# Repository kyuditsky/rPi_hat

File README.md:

9-70VDCin:: 5V 3A Vout buck converter

see buildnotes_rpi_hat.txt for up to date notes/info

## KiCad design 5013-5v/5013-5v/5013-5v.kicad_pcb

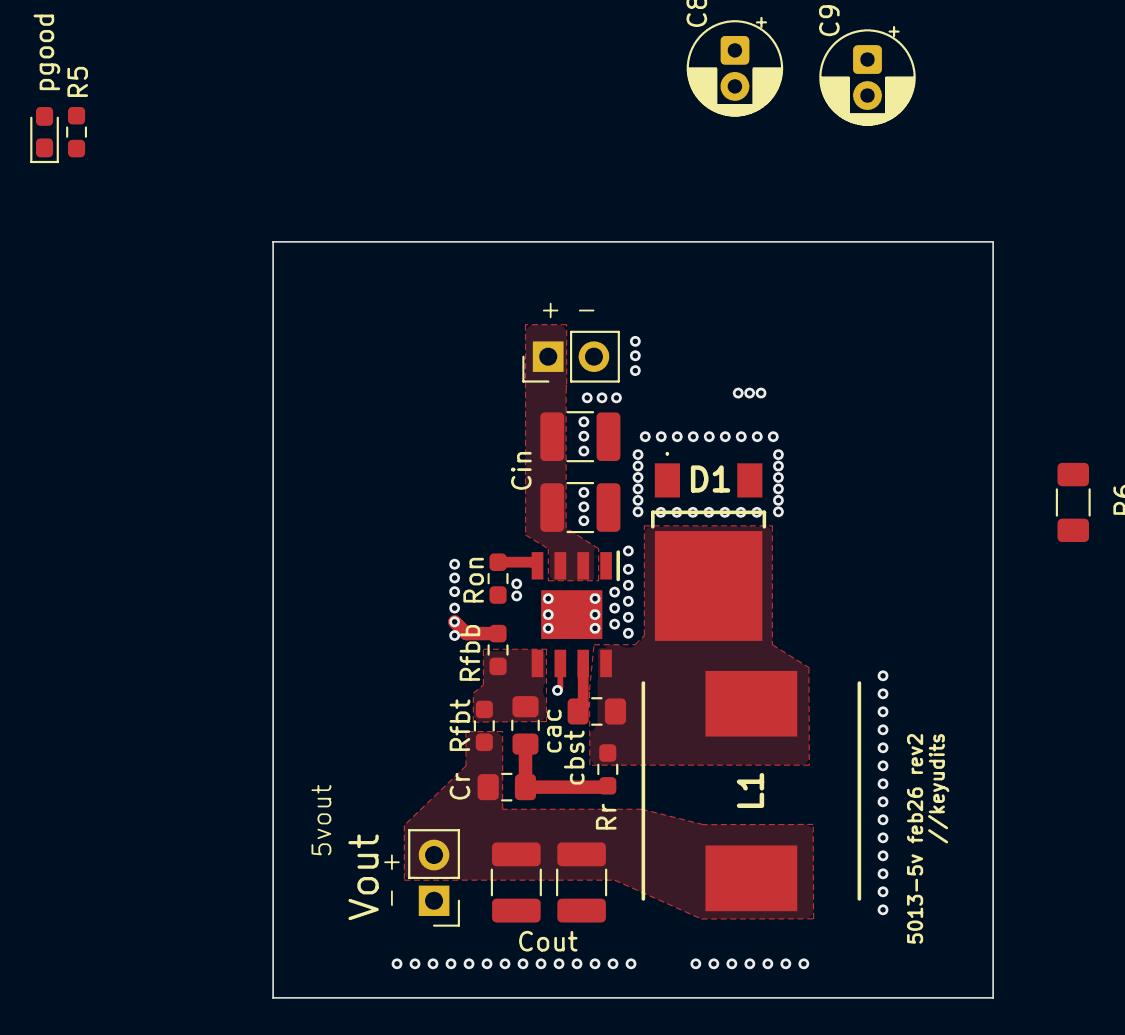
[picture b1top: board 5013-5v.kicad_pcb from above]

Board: 2 copper layers, 40.0 x 42.0 mm, 21 parts (0 on the bottom side), 11 nets.

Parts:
C8, C9: C_Polarized; CP_Radial_D5.0mm_P2.00mm
Cin: 2.2u; C_1210_3225Metric_Pad1.33x2.70mm_HandSolder
Cin#2: 2.2uF; C_1210_3225Metric_Pad1.33x2.70mm_HandSolder
Cout: 22uF; C_1210_3225Metric_Pad1.33x2.70mm_HandSolder
Cout#2: 22uF; C_1210_3225Metric_Pad1.33x2.70mm_HandSolder
Cr: 3.3nF; C_0805_2012Metric_Pad1.18x1.45mm_HandSolder
D1: D_Schottky; TO-252-Ae-3
IC1: LM5013DDAR; SOIC127P600X170-9N
L1: 22uH; INDPM120120X1020N
R5: 2.2k; R_0603_1608Metric_Pad0.98x0.95mm_HandSolder
R6: 0; R_1206_3216Metric_Pad1.30x1.75mm_HandSolder
Rfbb: 49.9kOhm; R_0603_1608Metric_Pad0.98x0.95mm_HandSolder
Rfbt: 158kOhm; R_0603_1608Metric_Pad0.98x0.95mm_HandSolder
Ron: 41.2kOhm; R_0603_1608Metric_Pad0.98x0.95mm_HandSolder
Rr: 154kOhm; R_0603_1608Metric_Pad0.98x0.95mm_HandSolder
Vin: Conn_01x02_Pin; PinHeader_1x02_P2.54mm_Vertical
Vout: Conn_01x02_Pin; PinHeader_1x02_P2.54mm_Vertical
cac: 100pF; C_0805_2012Metric_Pad1.18x1.45mm_HandSolder
cbst: 2.2nF 50v X7R; C_0805_2012Metric_Pad1.18x1.45mm_HandSolder
pgood: LED; LED_0603_1608Metric_Pad1.05x0.95mm_HandSolder

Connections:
/Vin: C8.1, C9.1, Cin.1, Cin#2.1, IC1.2 (VIN), IC1.3 (EN/UVLO), Vin.1
/Vout: Cout.1, Cout#2.1, Cr.2, L1.2, Rfbt.1, Vout.2
/fb: IC1.5 (FB), Rfbb.1, Rfbt.2, cac.2
/sw: D1.1 (K), IC1.8 (SW), L1.1, Rr.1, cbst.1
GND: Cout.2, Cout#2.2, R6.1, Rfbb.2, Vout.1, pgood.1 (K)
GND1: C8.2, C9.2, Cin.2, Cin#2.2, D1.2 (A), IC1.1 (GND), IC1.9 (EP), R6.2, Ron.2, Vin.2
unnamed: Cr.1, Rr.2, cac.1
unnamed: IC1.7 (BST), cbst.2
unnamed: IC1.6 (PGOOD), R5.2
unnamed: IC1.4 (RON), Ron.1
unnamed: R5.1, pgood.2 (A)

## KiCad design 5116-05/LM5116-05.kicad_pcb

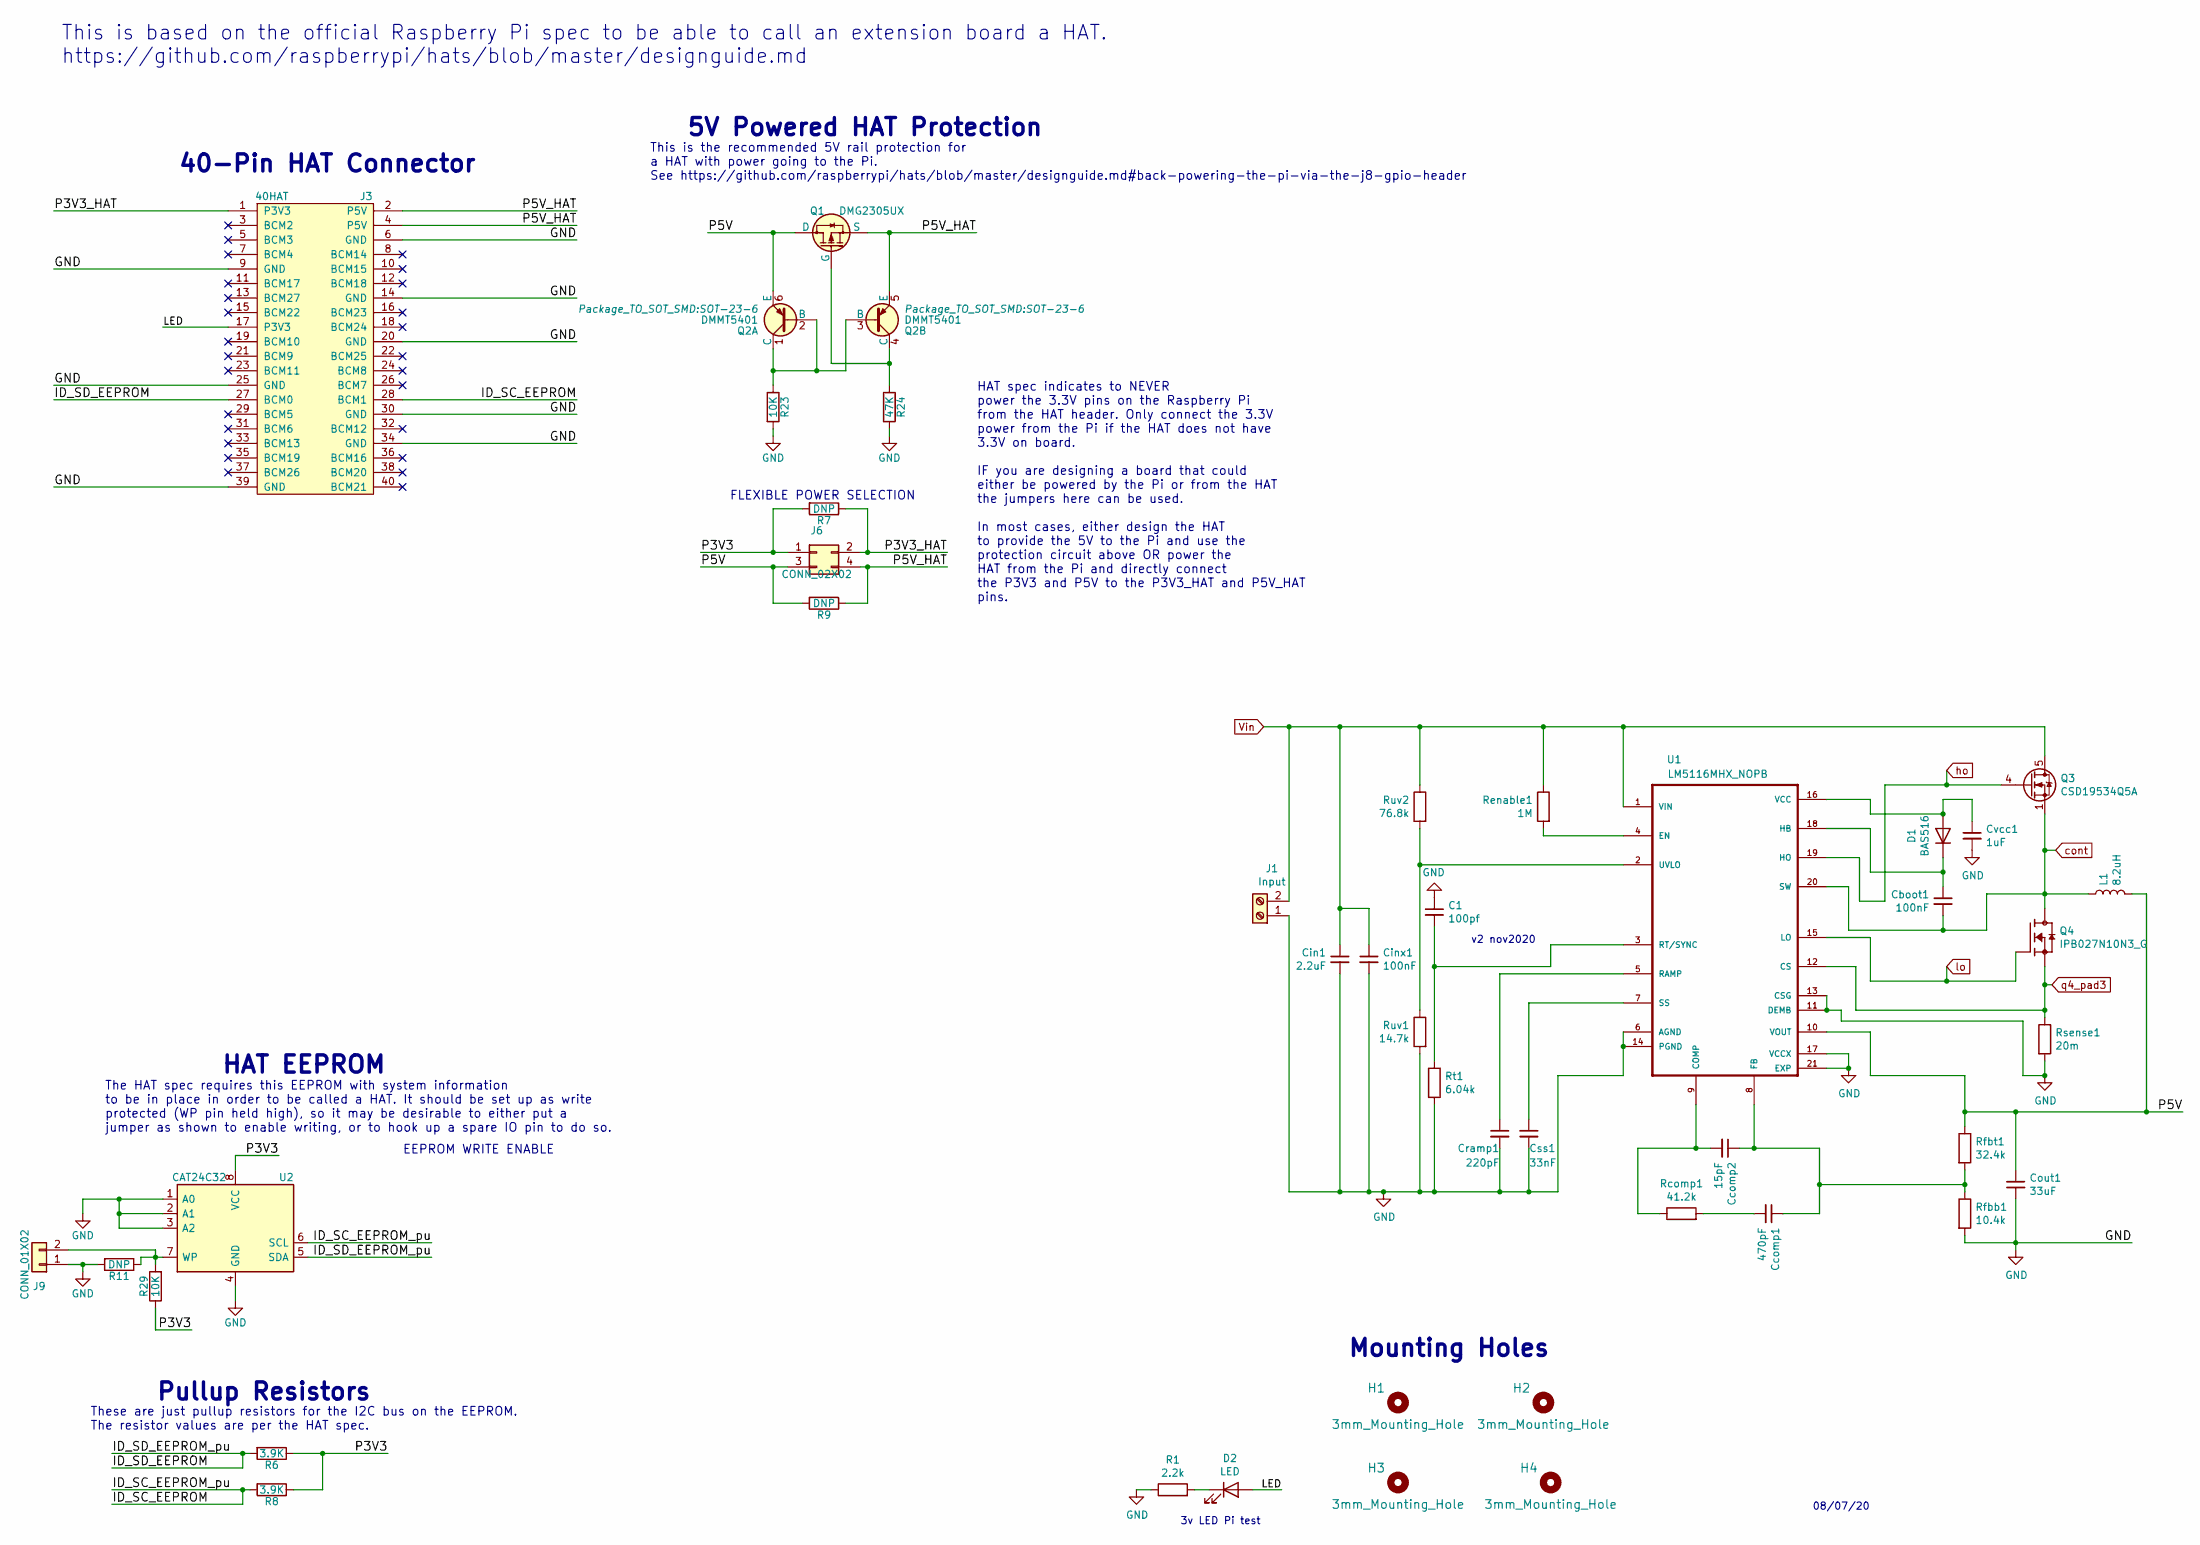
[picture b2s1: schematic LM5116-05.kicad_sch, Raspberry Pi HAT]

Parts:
C1: 100pf; C_Disc_D3.0mm_W2.0mm_P2.50mm
Cboot1: 100nF; C_0402_1005Metric
Ccomp1: 470pF; C_0402_1005Metric
Ccomp2: 15pF; C_0402_1005Metric
Cin1: 2.2uF; C_1210_3225Metric
Cinx1: 100nF; C_0805_2012Metric
Cout1: 33uF; C_1206_3216Metric
Cramp1: 220pF; C_0402_1005Metric
Css1: 33nF; C_0805_2012Metric
Cvcc1: 1uF; C_0805_2012Metric
D1: BAS516; D_SOD-523
D2: LED; LED_0805_2012Metric
H1, H2, H3, H4: 3mm_Mounting_Hole; NPTH_3mm_ID
J1: Input; TerminalBlock_bornier-2_P5.08mm
J3: 40HAT; PinSocket_2x20_P2.54mm_Vertical
J6: CONN_02X02; PinHeader_2x02_P2.54mm_Vertical
J9: CONN_01X02; PinHeader_1x02_P2.54mm_Vertical
L1: 8.2uH; L_Bourns_SRP6540
Q1: DMG2305UX; SOT-23
Q2: DMMT5401; SOT-23-6
Q3: CSD19534Q5A; TDSON-8-1
Q4: IPB027N10N3_G; TO254P1524X457-4N
R1: 2.2k; R_0805_2012Metric
R6, R8: 3.9K; R_0603_1608Metric_Pad0.84x1.00mm_HandSolder
R7, R9, R11: DNP; R_0603_1608Metric_Pad0.84x1.00mm_HandSolder
R23, R29: 10K; R_0603_1608Metric_Pad0.84x1.00mm_HandSolder
R24: 47K; R_0603_1608Metric_Pad0.84x1.00mm_HandSolder
Rcomp1: 41.2k; R_0402_1005Metric
Renable1: 1M; R_0402_1005Metric
Rfbb1: 10.4k; R_0805_2012Metric
Rfbt1: 32.4k; R_0402_1005Metric
Rsense1: 20m; R_1206_3216Metric
Rt1: 6.04k; R_0402_1005Metric
Ruv1: 14.7k; R_0805_2012Metric
Ruv2: 76.8k; R_0805_2012Metric
U1: LM5116MHX_NOPB; SOP65P640X120-21N; Manufacturer_Part_Number LM5116MH/NOPB; Mouser Part Number 926-LM5116MH/NOPB
U2: CAT24C32; SOIC-8_3.9x4.9mm_P1.27mm

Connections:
/ID_SC_EEPROM: J3.28 (BCM1), R8.2, U2.6 (SCL)
/ID_SD_EEPROM: J3.27 (BCM0), R6.2, U2.5 (SDA)
/LED: D2.2 (A), J3.17 (P3V3)
/P3V3: J6.1, R6.1, R7.2, R8.1, R29.1, U2.8 (VCC)
/P3V3_HAT: J3.1 (P3V3), J6.2, R7.1
/P5V: Cout1.1, J6.3, L1.2, Q1.3 (D), Q2.6 (E), R9.2, Rfbt1.1, U1.10 (VOUT); also elsewhere on the board
/P5V_HAT: J3.2 (P5V), J3.4 (P5V), J6.4, Q1.2 (S), Q2.5 (E), R9.1
GND: C1.1, Cin1.2, Cinx1.2, Cout1.2, Cramp1.2, Css1.2, Cvcc1.2, J1.1, J3.6 (GND), J3.9 (GND), J3.14 (GND), J3.20 (GND), J3.25 (GND), J3.30 (GND), J3.34 (GND), J3.39 (GND), J9.1, R1.1, R11.2, R23.2, R24.2, Rfbb1.2, Rsense1.2, Rt1.2, Ruv1.2, U1.6 (AGND), U1.11 (DEMB), U1.13 (CSG), U1.14 (PGND), U1.17 (VCCX), U1.21 (EXP), U2.1 (A0), U2.2 (A1), U2.3 (A2), U2.4 (GND); also elsewhere on the board
unnamed 8: C1.2, Rt1.1, U1.3 (RT/SYNC); also elsewhere on the board
unnamed: Cboot1.1, D1.1 (K), U1.18 (HB)
unnamed: Ccomp1.1, Ccomp2.1, Rfbb1.1, Rfbt1.2, U1.8 (FB)
unnamed: Ccomp1.2, Rcomp1.2
unnamed: Ccomp2.2, Rcomp1.1, U1.9 (COMP)
unnamed: Cramp1.1, U1.5 (RAMP)
unnamed: Css1.1, U1.7 (SS)
unnamed: Cvcc1.1, D1.2 (A), U1.16 (VCC)
unnamed: D2.1 (K), R1.2
unnamed: J9.2, R11.1, R29.2, U2.7 (WP)
unnamed: Q1.1 (G), Q2.4 (C), R24.1
unnamed: Q2.1 (C), Q2.2 (B), Q2.3 (B), R23.1
unnamed 20: Renable1.2, U1.4 (EN); also elsewhere on the board
unnamed: Ruv1.1, Ruv2.2, U1.2 (UVLO)
Vin: Cin1.1, Cinx1.1, J1.2, Q3.5 (D), Renable1.1, Ruv2.1, U1.1 (VIN)
cont: Cboot1.2, L1.1, Q3.1 (S), Q3.2 (S), Q3.3 (S), Q4.2, U1.20 (SW); also elsewhere on the board
ho: Q3.4 (G), U1.19 (HO)
lo: Q4.1, U1.15 (LO)
q4_pad3: Q4.3, Rsense1.1, U1.12 (CS)

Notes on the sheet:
3v LED Pi test
This is the recommended 5V rail protection for a HAT with power going to the Pi. See https://github.com/raspberrypi/hats/blob/master/designguide.md#back-powering-the-pi-via-the-j8-gpio-header
5V Powered HAT Protection
08/07/20
HAT EEPROM
Pullup Resistors
The HAT spec requires this EEPROM with system information to be in place in order to be called a HAT. It should be set up as write protected (WP pin held high), so it may be desirable to either put a jumper as shown to enable writing, or to hook up a spare IO pin to do so.
This is based on the official Raspberry Pi spec to be able to call an extension board a HAT. https://github.com/raspberrypi/hats/blob/master/designguide.md
HAT spec indicates to NEVER power the 3.3V pins on the Raspberry Pi from the HAT header. Only connect the 3.3V power from the Pi if the HAT does not have 3.3V on board. IF you are designing a board that could either be powered by the Pi or from the HAT the jumpers here can be used. In most cases, e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
EEPROM WRITE ENABLE
These are just pullup resistors for the I2C bus on the EEPROM. The resistor values are per the HAT spec.
v2 nov2020
40-Pin HAT Connector
Mounting Holes
FLEXIBLE POWER SELECTION

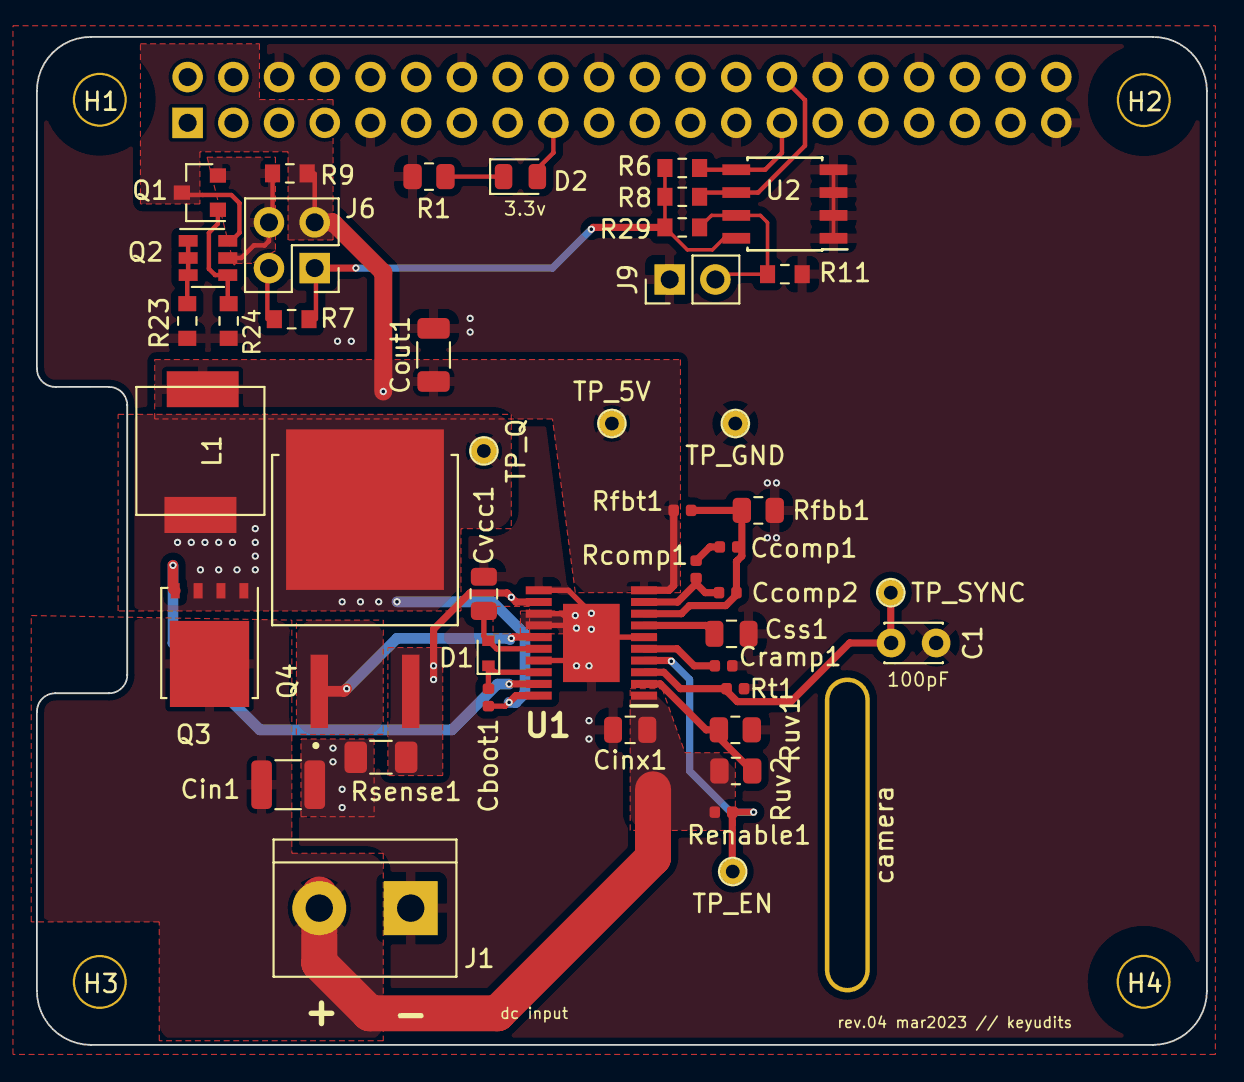
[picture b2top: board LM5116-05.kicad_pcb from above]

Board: 2 copper layers, 65.0 x 56.0 mm, 50 parts (1 on the bottom side), 27 nets.

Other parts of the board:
TP_5V: test_point
TP_EN: test_point
TP_GND: test_point
TP_Q: test_point
TP_SYNC: test_point
camera: raspberry_pi_camera_cutout

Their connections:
/P5V: TP_5V.1; also elsewhere on the board
GND: TP_GND.1; also elsewhere on the board
unnamed 8: TP_SYNC.1; also elsewhere on the board
unnamed 20: TP_EN.1; also elsewhere on the board
cont: TP_Q.1; also elsewhere on the board

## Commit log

2023-02-01 added gitignore
2023-02-01 routed V05
2023-02-01 Added Gerbers
2023-02-15 Fixed ho copper pour
2025-11-10 updating working tree
2025-11-10 added LM5013-5V, schematic capture
2025-11-11 added rev4 powerhat testing to buildnotes
2025-11-13 moved hat layout to new folder, focusing on LM5013
2025-11-13 added regulators, rough layout
2025-11-17 5013 rough layout complete
2025-11-17 routed pcbnew, gathering bom
2025-11-18 added rev1BOM, fixed pours
2025-11-18 updated buildnote
2025-11-24 plotted rev1 gerbers
2025-12-02 built 5013-5vrev1, updated buildnotes
2025-12-16 updated buildnote with testing results'
2025-12-30 Updated buildnote with current sense data
2026-01-19 new tests with 10W resistors
2026-01-20 additional testing, microusb & breadboard ommision
2026-02-10 began 5013-5v rev2 pcbnew
